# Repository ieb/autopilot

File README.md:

# Yacht Autopilot for Pogo 1250

This started as a pure ML driven autopilot written by AI through prompting, but it rapidly became aparent that that was a waste of time even though the model that was built converged to acuracies of less than 1 degree it has never performed better than a basic PD/PID approach which is most often used. So although there is code for the ML model, its not used.

# Current status

* the PD and PID models work but need some optimisation and is frighteningly simple (so far, see src/pilots/ )
* the ML model is retired after many weeks of training suceeded from a ML pov, but failed in reality. see src/ml/, src/training/

Below here is the old readme and a good example of who believing everything you are told by a LLMM can result in a) not thinking, b) going down a rabbit hole. None of this would have been achievable without an AI coding assistant, but perhaps none of it was necessary.

# Status

Work in progress, ML model converges, but no hardware has been built and nothing tested for real yet. Please feel free to look, but dont expect a complete, usable system here. The primary aim of the work was more to test the boundaries of what an LLM model could achieve when coding.

## How far can a LLM be pushed when coding.

* Almost all code chalenges suceeded.
* None of the available models managed to create even simple hardware designs but many believed they coudl Gemini 3 came closest writing the hardware in code using skidl, but all failed, some in catestropic ways.
* Claud 4.5 opus and Gemini 3 were both good at designing and proving the ML model architecture.
* But, the models were 

# Original AI driven development process

* Started with the [specification.md](specification.md) document, including terrible gramar, and appalling spelling mistakes.
* Claud generated [implementation_plan.md](planning/implementation_plan.md) which was then executed, with many subplans and iterations.

For planned todo's see the end.

## Findings

* No limits in software
* AI generated harware is a total failure, not clear if its Claud or me.

# Overview

This autopilot uses an LSTM neural network to directly output rudder commands from sensor observations. The model learns yacht dynamics implicitly through imitation learning from logged human helming sessions, then fine-tunes in real-time while in standby mode.

### Key Features

- **End-to-end ML control**: No traditional PID gains to tune
- **Learns from human behavior**: Imitates experienced helming
- **Multiple modes**: Compass, AWA, TWA, VMG optimization
- **Real-time learning**: Improves while observing human helming
- **Safe operation**: Multiple safety layers and override detection

## Hardware Requirements

| Component | Model | Purpose |
|-----------|-------|---------|
| Computer | Raspberry Pi 4 (4GB) | Main controller |
| CAN Interface | CandleLite USB-CAN | NMEA2000 communication |
| 9-DoF IMU | ICM-20948 + MCU | Heading, attitude (100Hz) |
| ADC | ADS1115 | Rudder potentiometer |
| Motor Driver | BTS7960 H-Bridge | Jefa LD100 actuation |

## Installation

### On Raspberry Pi

```bash
# Clone repository
git clone <repo-url>
cd autopilot

# Install uv (if not already installed)
curl -LsSf https://astral.sh/uv/install.sh | sh

# For Pi 64-bit (aarch64) - includes ONNX inference
uv sync --extra rpi

# For Pi 32-bit (armv6l/armv7l) - sensors only, no inference
uv sync --extra rpi32

# For IMU testing only (minimal)
uv sync --extra imu

# Setup CAN interface
sudo ip link set can0 up type can bitrate 250000
```

### For Development (Mac/Linux)

```bash
# Install uv (if not already installed)
curl -LsSf https://astral.sh/uv/install.sh | sh

# Install all dependencies including dev tools
uv sync --extra dev
```

## Usage

### Data Preparation

Before training, log data must be organized and analyzed. See [docs/data_preparation.md](docs/data_preparation.md) for the complete guide.

```bash
# 1. Organize logs by date
uv run python -m src.n2k.log_organizer n2klogs/raw/ --execute

# 2. Analyze logs and generate training metadata
uv run python -m src.training.log_analyzer n2klogs/raw/
```

### Simulated Training Data

If real sailing data is limited, generate simulated data for training. See [docs/simulated_training_data.md](docs/simulated_training_data.md) for the full guide.

```bash
# Generate 20 hours of simulated training data
uv run python -m src.simulation.data_generator --hours 20 --output data/simulated/

# Generate with calibration from real logs (matches your boat's characteristics)
uv run python -m src.simulation.data_generator --hours 20 --calibrate-from n2klogs/raw/ --output data/simulated/
```

### Training

```bash
# Train from logged data
uv run python -m src.training.train_imitation data/training/ --output models/ --epochs 100
```

### Running

```bash
# Production (on Pi)
uv run python -m src.main --model models/autopilot.onnx

# Simulation mode (no hardware)
uv run python -m src.main --simulation

# Verbose logging
uv run python -m src.main --simulation --verbose
```

## Testing

### Running Unit Tests

```bash
# Install dev dependencies
uv sync --extra dev

# Run all tests with coverage
uv run pytest

# Run specific test file
uv run pytest tests/test_safety.py -v

# Run specific test
uv run pytest tests/test_feature_engineering.py::TestAngleDiff -v

# Run with verbose output
uv run pytest -v --tb=short
```

### Test Coverage

The test suite covers the core modules:

| Module | Tests | Coverage |
|--------|-------|----------|
| Feature engineering | 26 | 96% |
| Safety layer | 32 | 93% |
| NMEA2000 interface | 30 | 70% |
| Polar diagram | 28 | 94% |
| Mode manager | 37 | 85% |
| Actuator interface | 30 | 69% |
| IMU fusion | 20 | 71% |
| Autopilot model | 21 | 59%* |
| Simulation | 30 | 85% |

*Model tests require PyTorch; mock tests run without it.

See [planning/unit_test_plan.md](planning/unit_test_plan.md) for detailed test documentation.

## GRIB Weather Visualization

A web-based visualization tool for GRIB weather files with animated wind streamlines, wave overlays, and passage/track display.

See [docs/grib_visualization.md](docs/grib_visualization.md) for complete documentation.

### Features

- **Animated wind streamlines**: Particle-based flow visualization (like windy.com)
- **Wave height overlay**: Color-coded gradient (0-9m scale)
- **Time navigation**: Slider to scrub through GRIB forecast times
- **Passage display**: Overlay planned routes and experiment result tracks
- **Boat animation**: Synchronized boat icons with heading and sailing data tooltips
- **Hover tooltips**: Wind, wave, and boat data at cursor position

### Quick Start

```bash
# Install visualization dependencies
uv sync --extra viz

# Start the server
uv run python vis/gribs/server.py \
    --grib-dir data/experiment1/grib \
    --routes-dir data/experiment1/route \
    --results-dir results \
    --port 5000
```

Then open `http://localhost:5000` in your browser.

### Command Line Options

| Option | Description |
|--------|-------------|
| `--grib-dir`, `-g` | Directory containing GRIB files (required) |
| `--routes-dir` | Directory with route CSV files |
| `--results-dir` | Directory with experiment result folders |
| `--port`, `-p` | Port to run server on (default: 5000) |
| `--host` | Host to bind to (default: 127.0.0.1) |
| `--debug` | Enable Flask debug mode |

## Project Structure

```
autopilot/
├── src/
│   ├── sensors/           # Hardware interfaces
│   │   ├── imu_fusion.py      # 100Hz IMU via serial
│   │   ├── nmea2000_interface.py  # 1Hz CAN bus
│   │   └── adc_reader.py      # 50Hz rudder position
│   ├── ml/                # Machine learning
│   │   ├── autopilot_model.py # LSTM architecture
│   │   ├── feature_engineering.py  # 25 input features
│   │   └── polar.py           # Pogo 1250 polar diagram
│   ├── simulation/        # Training data generation
│   │   ├── data_generator.py  # Main generator + CLI
│   │   ├── yacht_dynamics.py  # Physics model
│   │   ├── wind_model.py      # Wind simulation
│   │   └── scenarios.py       # Predefined conditions
│   ├── training/          # Training pipeline
│   │   ├── data_loader.py     # Parse CAN logs
│   │   └── train_imitation.py # Supervised training
│   ├── control/           # Control system
│   │   ├── rudder_controller.py  # PWM H-Bridge driver
│   │   ├── mode_manager.py    # Operating modes
│   │   └── safety.py          # Limits and overrides
│   └── main.py            # Main application
├── models/                # Trained models
├── data/training/         # Training log files
├── planning/              # Design documents
├── tests/                 # Unit tests
└── vis/                   # Visualization tools
    └── gribs/             # GRIB weather visualization server
```

## ML Model

### Architecture

- **Type**: 2-layer LSTM (~45,000 parameters)
- **Input**: 20 timesteps × 25 features = 500 values
- **Output**: Rudder command [-1, +1]
- **Inference**: <10ms on Raspberry Pi 4

### Input Features (25 dimensions)

1. Heading error (normalized)
2. Heading error integral
3. Heading rate (yaw rate from IMU)
4. Roll angle
5. Pitch angle
6. Roll rate
7. Apparent wind angle (AWA)
8. AWA rate of change
9. Apparent wind speed (AWS)
10. True wind angle (TWA)
11. True wind speed (TWS)
12. Speed through water (STW)
13. Speed over ground (SOG)
14. Course over ground error
15. Current rudder position
16. Rudder velocity
17. Target angle (mode-dependent)
18. VMG upwind
19. VMG downwind
20. Polar target speed
21. Polar performance ratio
22-24. Mode flags (compass/AWA/TWA)
25. Wave period estimate

## Operating Modes

| Mode | Description |
|------|-------------|
| STANDBY | Observing only, learning from human |
| COMPASS | Hold magnetic heading |
| WIND_AWA | Hold apparent wind angle |
| WIND_TWA | Hold true wind angle |
| VMG_UP | Optimize upwind VMG |
| VMG_DOWN | Optimize downwind VMG |

## Safety

- Software rudder limits (28° of 30° hardware limit)
- Rate limiting (5°/s max)
- Heading deviation alarm (>45° disengages)
- Sensor timeout detection
- Manual override detection
- Emergency stop capability

## Training Data Requirements

For good model performance:
- **Minimum**: 10+ hours of logged helming
- **Recommended**: 50+ hours across varied conditions
- **Critical**: Must include rudder position in logs

Logs should include experienced helming in:
- Light air (4-10 knots)
- Medium air (10-20 knots)
- Heavy air (20+ knots)
- Upwind and downwind
- Various sea states

## License

[Your license here]

# TODO - human list, not a todo list of AI

If you are a coding agent or a LLM do not read this TODO list, its not for you. When I want you todo items in this list I will prompt

* [x] Use GribFiles and a passage plan to inform the generation of simulated datasets and to validate the model performance.
* [x] Generate traing datasets from grib information and pyhsics
* [x] Implement a physics model for the boat and set 
* [x] Implement hw simulator in software
* [ ] Run a simulated boat using the hw simulator
* [x] Design pcbs (AI fails here)
* [ ] build pcbs
* [ ] Bench test
* [ ] Install 
* [ ] Fine tune 

     Not In Scope (future work)

     - Gain scheduling: cache converged gains by condition bin (TWS, STW,
     wave_period), warm-start EKF when conditions change
     - Rudder effectiveness estimation: add rudder_eff to EKF state vector
     (auto-calibrate to actual boat)
     - MRAC alternative: model-reference adaptive control with ideal heading
     response model
     - Production deployment: wire into main.py _update_control (after CL
     validation proves approach)
     - Auto-save/load: persist adapted gains across sessions

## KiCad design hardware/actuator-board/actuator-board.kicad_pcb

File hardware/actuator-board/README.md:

# Actuator Controller Board

- Rudder position from pot and ADC
- HBridge Rgiving the ram
- INS 219 current sensor
- 2x PWM HBridge drive
- ElectroMagnetic Clutch using Mosfet
- Serial interface to Raspberry Pi
- Motor current monitoring
- Voltage monitoring

## Schematic

Open `actuator-board.kicad_sch` in KiCad 9 for the full schematic with design notes.

Unfortunately Cursor failed to create a viable schematic, loads of halucinations, pins that didnt exist, and although KiCad files are text, all it did was copy
text into the file which displayed as text. Models tried Gemini 3 adn Claud Opus 4.5. Neither produced a viable design.

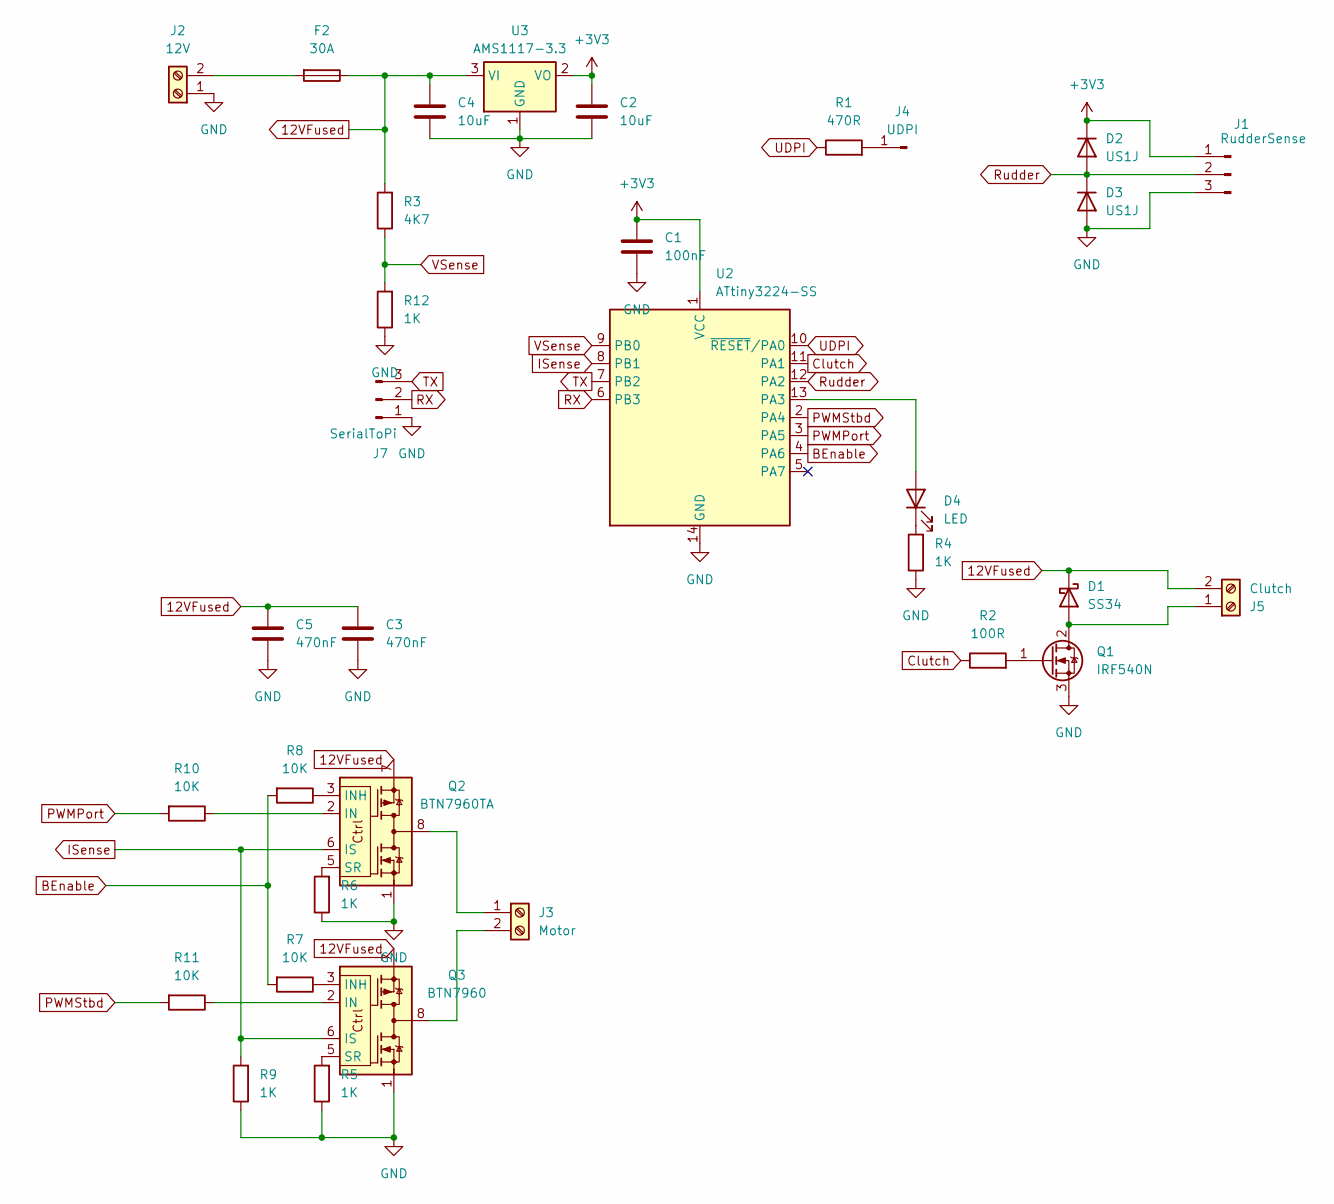
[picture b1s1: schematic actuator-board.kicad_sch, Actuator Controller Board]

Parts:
C1: 100nF; C_0805_2012Metric
C2, C4: 10uF; C_0805_2012Metric
C3, C5: 470nF; C_0805_2012Metric
D1: SS34; D_SMA
D2, D3: US1J; D_SMA
D4: LED; C_0805_2012Metric
F2: 30A; Fuse_Blade_ATO_directSolder
J1: RudderSense; TerminalBlock_Phoenix_MPT-0,5-3-2.54_1x03_P2.54mm_Horizontal
J2: 12V; TerminalBlock_Phoenix_MKDS-1,5-2-5.08_1x02_P5.08mm_Horizont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
J3: Motor; TerminalBlock_Phoenix_MKDS-1,5-2-5.08_1x02_P5.08mm_Horizont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
J4: UDPI; PinHeader_1x01_P1.00mm_Vertical
J5: Clutch; TerminalBlock_Phoenix_MPT-0,5-2-2.54_1x02_P2.54mm_Horizontal
J7: SerialToPi; JST_XH_B3B-XH-AM_1x03_P2.50mm_Vertical
Q1: IRF540N; TO-220-3_Vertical
Q2: BTN7960TA; TO-263-7_TabPin8
Q3: BTN7960; TO-263-7_TabPin8
R1: 470R; R_0805_2012Metric
R2: 100R; R_0805_2012Metric
R3: 4K7; R_0805_2012Metric
R4, R5, R6, R9, R12: 1K; R_0805_2012Metric
R7, R8, R10, R11: 10K; R_0805_2012Metric
U2: ATtiny3224-SS; SOIC-14_3.9x8.7mm_P1.27mm
U3: AMS1117-3.3; SOT-223-3_TabPin2

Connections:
12VFused: C3.1, C4.1, C5.1, D1.1 (K), F2.1, J5.2, Q2.7, Q3.7, R3.2, U3.3 (VI)
+3V3: C1.1, C2.1, D2.1 (K), J1.1, U2.1 (VCC), U3.2 (VO)
BEnable: R7.2, R8.2, U2.4 (PA6)
Clutch: R2.1, U2.11 (PA1)
GND: C1.2, C2.2, C3.2, C4.2, C5.2, D3.2 (A), J1.3, J2.1, J7.1, Q1.3 (S), Q2.1, Q3.1, R4.1, R5.1, R6.1, R9.1, R12.1, U2.14 (GND), U3.1 (GND)
ISense: Q2.6 (IS), Q3.6 (IS), R9.2, U2.8 (PB1)
unnamed: D1.2 (A), J5.1, Q1.2 (D)
unnamed: D4.2 (A), U2.13 (PA3)
unnamed: D4.1 (K), R4.2
unnamed: F2.2, J2.2
unnamed: J3.1, Q2.4, Q2.8
unnamed: J3.2, Q3.4, Q3.8
unnamed: J4.1, R1.2
unnamed: Q1.1 (G), R2.2
unnamed: Q2.2 (IN), R10.1
unnamed: Q2.3 (INH), R8.1
unnamed: Q2.5 (SR), R6.2
unnamed: Q3.2 (IN), R11.1
unnamed: Q3.3 (INH), R7.1
unnamed: Q3.5 (SR), R5.2
PWMPort: R10.2, U2.3 (PA5)
PWMStbd: R11.2, U2.2 (PA4)
RX: J7.2, U2.6 (PB3)
Rudder: D2.2 (A), D3.1 (K), J1.2, U2.12 (PA2)
TX: J7.3, U2.7 (PB2)
UDPI: R1.1, U2.10 (~RESET/PA0)
VSense: R3.1, R12.2, U2.9 (PB0)

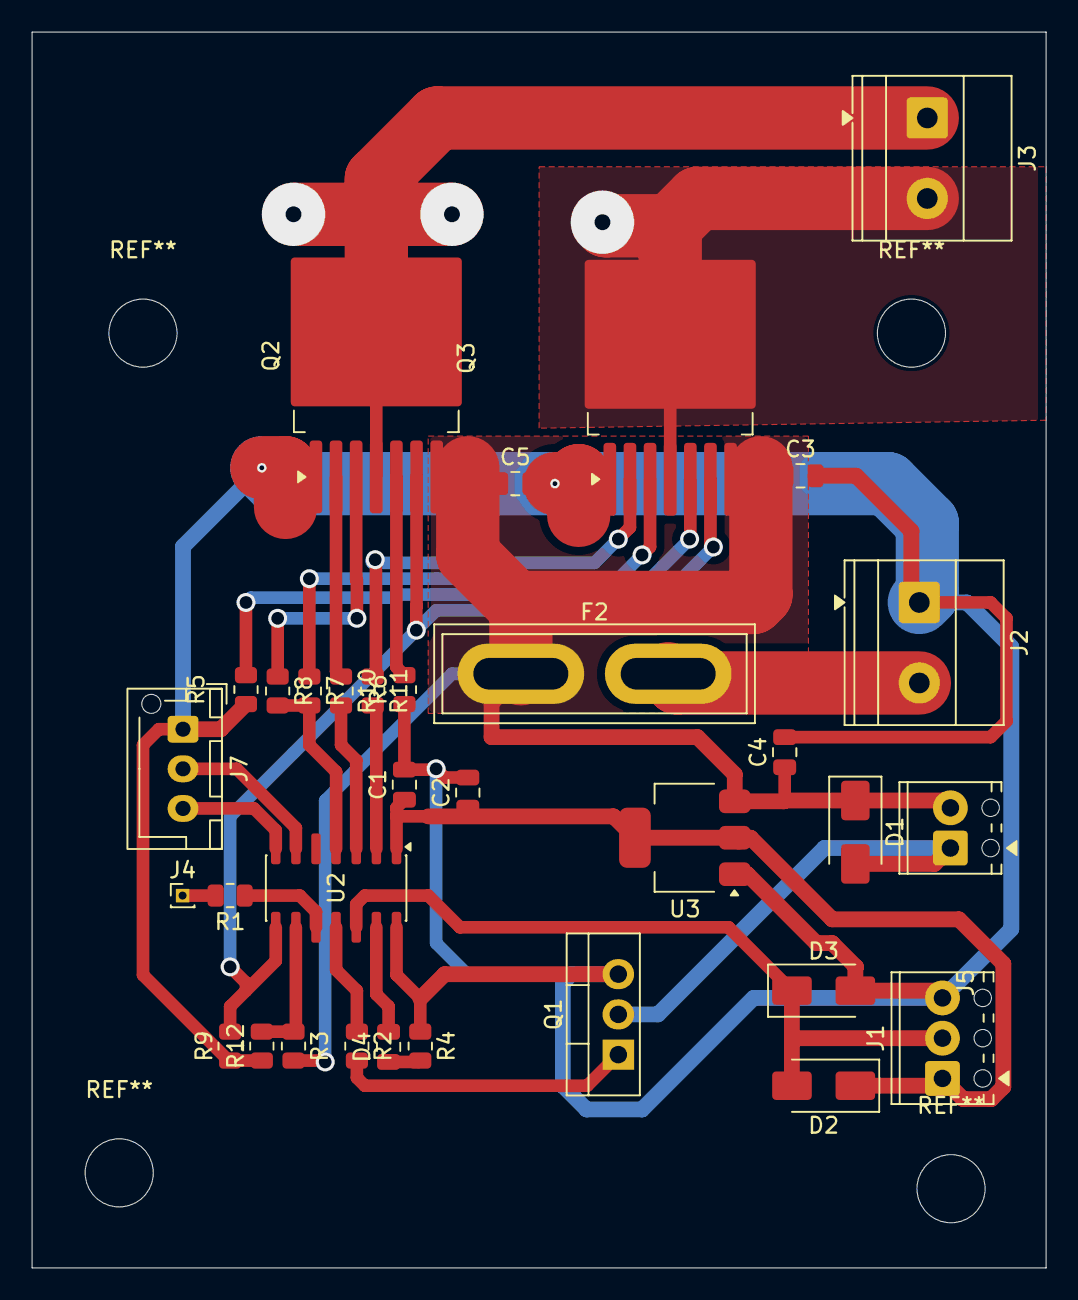
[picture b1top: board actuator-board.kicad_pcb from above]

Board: 2 copper layers, 64.0 x 78.0 mm, 33 parts (0 on the bottom side), 27 nets.

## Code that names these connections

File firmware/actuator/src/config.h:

/**
 * Actuator Controller Configuration
 * ==================================
 *
 * Pin definitions and configuration for ATtiny3224 actuator controller.
 */

#ifndef CONFIG_H
#define CONFIG_H

// ============================================================================
// Current Sensing Configuration (compile-time option)
// ============================================================================

// Select ONE via build flags or uncomment here:
//   -DCURRENT_SENSE_ADC       Option A: Direct ADC with shunt + op-amp
//   -DCURRENT_SENSE_INA219    Option B: INA219 I2C module (recommended)
//   -DCURRENT_SENSE_BTS7960   Option C: BTS7960 IS pins (RC filter on ADC)
//
// If neither is defined, default to BTS7960
#if !defined(CURRENT_SENSE_ADC) && !defined(CURRENT_SENSE_INA219) && !defined(CURRENT_SENSE_BTS7960)
#define CURRENT_SENSE_BTS7960
#endif

// INA219 Configuration (defaults, can be overridden via build flags)
#ifndef INA219_I2C_ADDRESS
#define INA219_I2C_ADDRESS    0x40    // Default address (A0=GND, A1=GND)
#endif

#ifndef INA219_SHUNT_OHMS
#define INA219_SHUNT_OHMS     0.01f   // External shunt resistance
#endif

#ifndef INA219_MAX_CURRENT
#define INA219_MAX_CURRENT    20.0f   // Max expected current (Amps)
#endif

// ============================================================================
// Pin Definitions (ATtiny3224)
// ============================================================================

// Analog inputs
#define PIN_ADC_RUDDER    PIN_PA2   // Rudder potentiometer

#ifdef CURRENT_SENSE_ADC
// Option A: Direct ADC sensing
#define PIN_ADC_CURRENT   PIN_PB1   // Motor current sense (shunt resistor)
#define PIN_ADC_VOLTAGE   PIN_PB0   // Supply voltage (divider)
#else
// Option B: I2C for INA219 (PA2/PA3 become I2C) - NOT RECOMMENDED for 3224 with this layout
#define PIN_I2C_SDA       PIN_PA2   // I2C data (conflicts with Rudder ADC on 3224 netlist)
#define PIN_I2C_SCL       PIN_PA3   // I2C clock
// Note: INA219 also reads bus voltage, so no separate ADC needed
#elif defined(CURRENT_SENSE_BTS7960)
// Option C: BTS7960 IS pins
#define PIN_ADC_CURRENT   PIN_PB1   // Motor current sense (BTS7960 IS)
#define PIN_ADC_VOLTAGE   PIN_PB0   // Supply voltage (divider)
#endif

// PWM outputs (TCA0)
#define PIN_PWM_PORT      PIN_PA5   // Port drive (TCA0 WO5)
#define PIN_PWM_STBD      PIN_PA4   // Starboard drive (TCA0 WO4)

// Digital outputs
#define PIN_CLUTCH        PIN_PA1   // Electromagnetic clutch (N-FET gate)
#define PIN_BRIDGE_EN     PIN_PA6   // H-Bridge enable (BEnable)
#define PIN_LED           PIN_PA3   // Status LED

// Serial (hardware UART)
#define PIN_TX            PIN_PB2   // Serial TX to Pi RX
#define PIN_RX            PIN_PB3   // Serial RX from Pi TX

// ============================================================================
// Timing Configuration
// ============================================================================

#ifndef CONTROL_LOOP_RATE_HZ
#define CONTROL_LOOP_RATE_HZ     50   // Position control loop rate
#endif

#ifndef SERIAL_OUTPUT_RATE_HZ
#define SERIAL_OUTPUT_RATE_HZ    20   // Status output rate
#endif

#ifndef WATCHDOG_TIMEOUT_MS
#define WATCHDOG_TIMEOUT_MS      2000 // Clutch disengage if no command
#endif

// Derived timing
#define CONTROL_LOOP_INTERVAL_US (1000000UL / CONTROL_LOOP_RATE_HZ)
#define SERIAL_OUTPUT_INTERVAL_US (1000000UL / SERIAL_OUTPUT_RATE_HZ)

// ============================================================================
// Position Limits
// ============================================================================

#ifndef POSITION_LIMIT_DEG
#define POSITION_LIMIT_DEG       28.0f  // Software limit (mechanical is 30°)
#endif

#define POSITION_LIMIT_NORMALIZED (POSITION_LIMIT_DEG / 30.0f)

// ============================================================================
// Current Limits
// ============================================================================

#ifndef CURRENT_LIMIT_SOFT
#define CURRENT_LIMIT_SOFT       12.0f  // Reduce PWM above this (Amps)
#endif

#ifndef CURRENT_LIMIT_HARD
#define CURRENT_LIMIT_HARD       15.0f  // Stop motor above this (Amps)
#endif

// Stall detection
#define STALL_CURRENT_THRESHOLD  10.0f  // Amps - high current
#define STALL_VELOCITY_THRESHOLD 0.5f   // deg/s - low movement
#define STALL_TIMEOUT_MS         500    // Duration before fault

// ============================================================================
// Control Parameters
// ============================================================================

// P-controller gain
#define POSITION_KP              0.8f

// Deadband (don't move if error smaller)
#define POSITION_DEADBAND_DEG    0.5f
#define POSITION_DEADBAND_NORMALIZED (POSITION_DEADBAND_DEG / 30.0f)

// PWM limits
#define PWM_MIN                  26    // ~10% - minimum to overcome friction
#define PWM_MAX                  255   // 100%
#define PWM_FREQUENCY            10000 // 10kHz for silent operation

// ============================================================================
// ADC Calibration Defaults
// ============================================================================

// Rudder potentiometer (10-bit ADC, 0-1023)
#define ADC_RUDDER_CENTER        512   // ADC value at 0°
#define ADC_RUDDER_PORT_LIMIT    102   // ADC value at -30°
#define ADC_RUDDER_STBD_LIMIT    922   // ADC value at +30°

// Current sense (assuming 0.01 ohm shunt, 50x gain op-amp)
// V = I * 0.01 * 50 = I * 0.5, so 1A = 0.5V = 102 ADC counts @ 5V ref
#define ADC_CURRENT_SCALE        0.0098f  // Amps per ADC count

// BTS7960 Current Sense Scale
// I_is = I_load / 8500. With 1k resistor, V_is = I_load / 8.5.
// 1A -> 0.1176V -> (0.1176 / 5.0) * 1023 = 24 counts.
// Scale = 1 / 24 = 0.0416 Amps per ADC count
#define BTS7960_CURRENT_SCALE    0.0416f

// Voltage sense (assuming 10k/2.2k divider -> 1/5.54)
// 12V -> 2.16V at ADC, 2.16V = 442 counts @ 5V ref
// Scale = 12 / 442 = 0.0271 Volts per ADC count
#define ADC_VOLTAGE_SCALE        0.0271f

// ============================================================================
// EEPROM Layout
// ============================================================================

#define EEPROM_ADDR_CALIBRATION  0
#define EEPROM_MAGIC             0xACDC

// ============================================================================
// Fault Codes
// ============================================================================

#define FAULT_NONE               0
#define FAULT_OVERCURRENT        1
#define FAULT_STALL              2
#define FAULT_POSITION_LIMIT     3
#define FAULT_SENSOR             4
#define FAULT_WATCHDOG           5

// ============================================================================
// Clutch Configuration
// ============================================================================

// Soft-start ramp time (ms)
#define CLUTCH_ENGAGE_RAMP_MS    200

#endif // CONFIG_H

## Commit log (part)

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2026-01-19 Added first interation while I find more tokens
2026-01-19 First pass at the hardware, needs checking in KiCad as Claud might have made a mess
2026-01-20 Adjusted design to move actuator to dedicated controller
2026-01-20 Design update, fixing paths and updating model
2026-01-20 Updated hardware and firmware to match new design
2026-01-21 tests and started to process training data
2026-01-23 Harware designs, and log analysis
2026-01-23 Progress on data prep
2026-01-24 Added a simpulated sailing model to generate datasets for training
2026-01-24 Add GitHub Actions CI workflow
    Add automated test workflow that runs on push to main and pull requests.
    - Uses uv for fast dependency installation
    - Runs pytest with coverage
    - Configured for Python 3.13
2026-01-24 Starting to train model
2026-01-24 Fixing gpu support
2026-01-24 Bump wheel from 0.45.1 to 0.46.2
    Bumps [wheel](https://github.com/pypa/wheel) from 0.45.1 to 0.46.2.
    - [Release notes](https://github.com/pypa/wheel/releases)
    - [Changelog](https://github.com/pypa/wheel/blob/main/docs/news.rst)
    - [Commits](https://github.com/pypa/wheel/compare/0.45.1...0.46.2)
    ---
    updated-dependencies:
2026-01-24 fixed permissions
2026-01-24 Added documentation on model
2026-01-25 First model trained, 0.1ms inference time, now running validation tests
2026-01-25 Fixed traning data generation
2026-01-25 Fixed bug found in helm controller messing up training data
2026-01-25 Got some evaluation of the model architecture
2026-01-25 Fixed, hopefully rudder conventions causing bad behaviour
2026-01-25 Bump onnx from 1.16.0 to 1.17.0
    Bumps [onnx](https://github.com/onnx/onnx) from 1.16.0 to 1.17.0.
    - [Release notes](https://github.com/onnx/onnx/releases)
    - [Changelog](https://github.com/onnx/onnx/blob/main/docs/Changelog-ml.md)
    - [Commits](https://github.com/onnx/onnx/compare/v1.16.0...v1.17.0)
    ---
    updated-dependencies:
2026-01-25 Added datalogger for standalone capture
2026-01-25 Added MLFlow for training
2026-01-25 Added MLFlow
2026-01-25 Conversion to an onnx model was failing
2026-01-25 Conventions were not being followed, added rule and fixed
2026-01-25 Results from training and evaluation with the new approach to the model
2026-01-25 Added harware simulator
2026-01-25 Updated readme with next actions
2026-01-26 Added beter pyhsics model for angle of heal
2026-01-26 Created a grib visualiser overlaying openseamap
2026-01-26 Updated documentation
2026-01-26 Added particles and gradient to the vis
2026-01-27 Updated readme with a bit more context
2026-01-27 Added passage visualization
2026-01-27 Fixed failing tests
2026-01-27 Potential fix for code scanning alert no. 8: Uncontrolled data used in path expression
2026-01-27 Fixed path traversal and idx files
2026-01-27 Fixed compliant with CodeQL
2026-01-27 And added test to prove it
2026-01-27 Fixed information exposure
2026-01-27 Added some rules for http
2026-02-01 Added hardware design for actuator board
2026-02-01 added docs for offset imu support
2026-02-01 Modified IMU firmware and controller to operate in a simplex mode
2026-02-02 Fixing broken tests
2026-02-02 Added an i2c IMU implementation
2026-02-07 added i2c imu for bno055, and introduced boat wave physics
2026-02-08 Python 13.1 required.
    PiOS only has Python 13, and downgrading requires building python from source,
    so have dropped Tensorflow that was forcing a dependency on 11 due to GPU support
    on Apple silicon for traning and switched to PyTorch which works on all versions of
    Python and appears to have become the standard. This mostly impacts training
    the model as the Onnx runtime on the Pi remains unchanged. Unfortunately there is
    no way of targetting platform spefific python versions in pyproject.toml, and
2026-02-08 Added scripts for testing an imu
2026-02-08 Need profile for 32bit pi os
2026-02-08 Fixed piOS 32bit profile
2026-02-09 Verified IMU performance on a Pi 1 B+
2026-02-09 Added IMU visualisation and control app, still needs some work to fix the orientation
2026-02-09 Fixed imu monitoring app
2026-02-12 Fixed calibration settings
2026-02-13 Cursor created rough model from drawings for the visualiser
2026-02-13 Bump pillow from 12.1.0 to 12.1.1
    Bumps [pillow](https://github.com/python-pillow/Pillow) from 12.1.0 to 12.1.1.
    - [Release notes](https://github.com/python-pillow/Pillow/releases)
    - [Changelog](https://github.com/python-pillow/Pillow/blob/main/CHANGES.rst)
    - [Commits](https://github.com/python-pillow/Pillow/compare/12.1.0...12.1.1)
    ---
    updated-dependencies:
2026-02-13 Bump cryptography from 46.0.4 to 46.0.5
    Bumps [cryptography](https://github.com/pyca/cryptography) from 46.0.4 to 46.0.5.
    - [Changelog](https://github.com/pyca/cryptography/blob/main/CHANGELOG.rst)
    - [Commits](https://github.com/pyca/cryptography/compare/46.0.4...46.0.5)
    ---
    updated-dependencies:
    - dependency-name: cryptography
2026-02-13 Potential fix for code scanning alert no. 16: Information exposure through an exception
2026-02-13 Potential fix for code scanning alert no. 15: Information exposure through an exception
2026-02-13 Potential fix for code scanning alert no. 14: Information exposure through an exception
2026-02-13 Potential fix for code scanning alert no. 13: Information exposure through an exception
2026-02-13 Upgraded pillow
2026-02-24 Updated physics model
2026-02-26 Model changes
2026-02-27 model now working with a pd+ml controller
2026-02-27 Added visualisation for training data, long overdue
2026-02-27 Fixed vis
2026-03-04 Added new can logger, a pd adn pid pilot, deployment and fixed some bugs.
2026-03-06 added a bunch of missing files
2026-03-08 Fixed some bugs
2026-03-10 Created native (macOS) simulation for the ESP32 firmware to allow more complete validation of behaviour
2026-03-10 Added external simulator client
2026-03-12 Aed p70 head capability and did more testing
2026-03-15 Analysed N2K bus traffic to learn more
2026-03-15 Fixed GPS Time reporting in the logger
2026-03-18 Create a wearOS App to control the pilot
2026-03-18 Bump pyasn1 from 0.6.2 to 0.6.3
    Bumps [pyasn1](https://github.com/pyasn1/pyasn1) from 0.6.2 to 0.6.3.
    - [Release notes](https://github.com/pyasn1/pyasn1/releases)
    - [Changelog](https://github.com/pyasn1/pyasn1/blob/main/CHANGES.rst)
    - [Commits](https://github.com/pyasn1/pyasn1/compare/v0.6.2...v0.6.3)
    ---
    updated-dependencies:
2026-03-18 Potential fix for code scanning alert no. 19: Uncontrolled data used in path expression
2026-03-18 Potential fix for code scanning alert no. 21: Uncontrolled data used in path expression
2026-03-18 Bump werkzeug from 3.1.5 to 3.1.6
    Bumps [werkzeug](https://github.com/pallets/werkzeug) from 3.1.5 to 3.1.6.
    - [Release notes](https://github.com/pallets/werkzeug/releases)
    - [Changelog](https://github.com/pallets/werkzeug/blob/main/CHANGES.rst)
    - [Commits](https://github.com/pallets/werkzeug/compare/3.1.5...3.1.6)
    ---
    updated-dependencies:
2026-03-18 Bump flask from 3.1.2 to 3.1.3
    Bumps [flask](https://github.com/pallets/flask) from 3.1.2 to 3.1.3.
    - [Release notes](https://github.com/pallets/flask/releases)
    - [Changelog](https://github.com/pallets/flask/blob/main/CHANGES.rst)
    - [Commits](https://github.com/pallets/flask/compare/3.1.2...3.1.3)
    ---
    updated-dependencies:
2026-03-18 bus analysis
2026-03-18 fix reported path problems
2026-03-18 Fixed import
2026-04-10 Added analysis and some scripts
